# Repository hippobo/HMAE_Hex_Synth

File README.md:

# HMAE_Hex_Synth

Hex Synth project with resistive touch pads based on ekkoflok hex synth project : https://www.ekkoflok.dk/hex.php

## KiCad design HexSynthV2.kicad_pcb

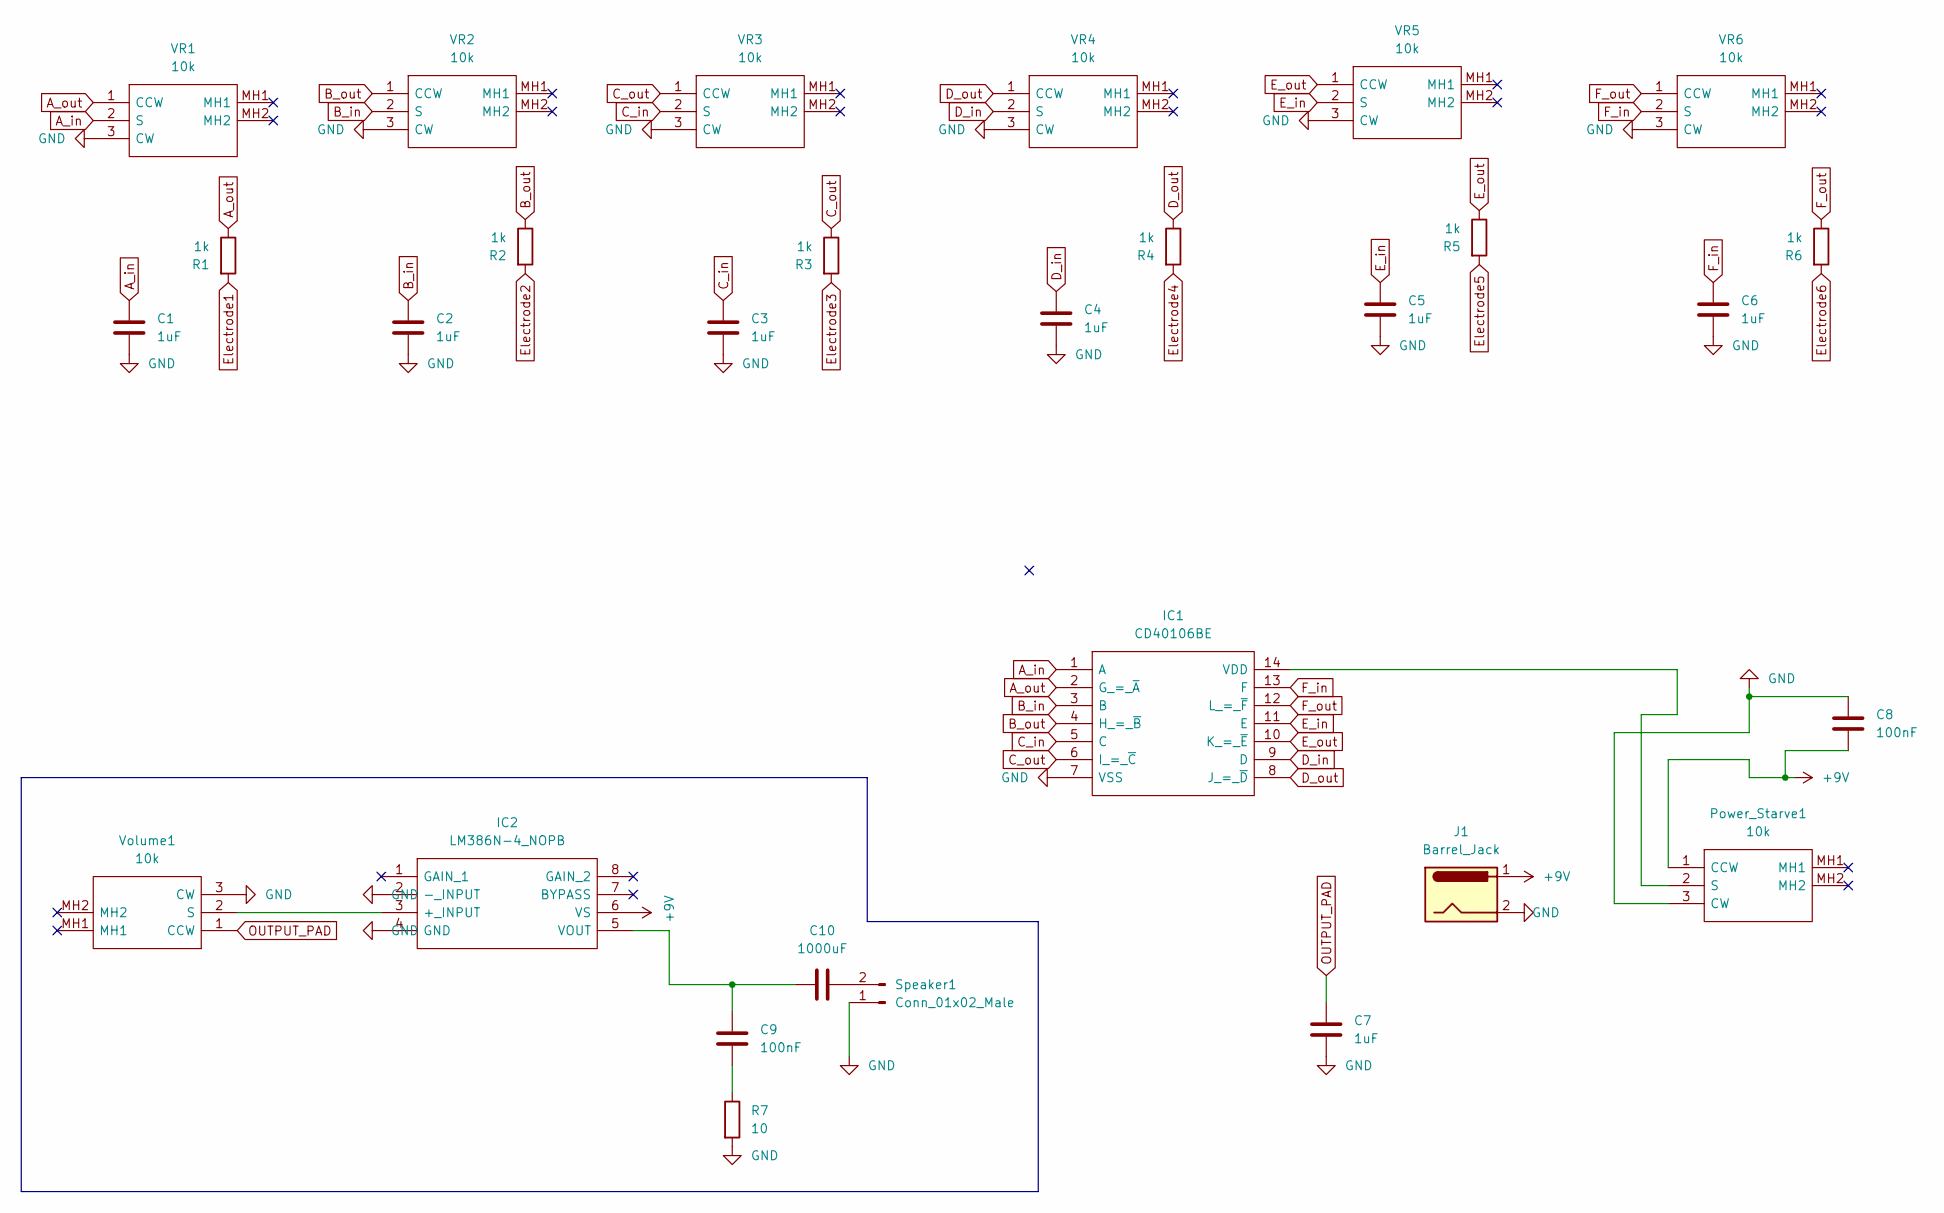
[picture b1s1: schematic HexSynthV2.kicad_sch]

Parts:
C1, C2, C3, C4, C5, C6, C7: 1uF; CP_Radial_D5.0mm_P2.50mm
C8, C9: 100nF; CP_Radial_D5.0mm_P2.50mm
C10: 1000uF; CP_Radial_D8.0mm_P5.00mm
IC1: CD40106BE; DIP794W53P254L1930H508Q14N; Mouser Part Number 595-CD40106BE
IC2: LM386N-4_NOPB; DIP794W53P254L959H508Q8N; Mouser Part Number 926-LM386N-4/NOPB
J1: Barrel_Jack; BarrelJack_Horizontal
Power_Starve1: 10k; P120PKY25BR10K; Mouser Part Number 858-P120PKY25BR10K
R1, R2, R3, R4, R5, R6: 1k; R_Axial_DIN0204_L3.6mm_D1.6mm_P2.54mm_Vertical
R7: 10; R_Axial_DIN0204_L3.6mm_D1.6mm_P2.54mm_Vertical
Speaker1: Conn_01x02_Male; PinHeader_1x02_P2.54mm_Vertical
VR1, VR2, VR3, VR4, VR5, VR6: 10k; P120PKY25BR10K; Mouser Part Number 858-P120PKY25BR10K
Volume1: 10k; P120PKY25BR10K; Mouser Part Number 858-P120PKY25BR10K

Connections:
+9V: C8.1, IC2.6 (VS), J1.1, Power_Starve1.1 (CCW)
A_in: C1.1, IC1.1 (A), VR1.2 (S)
A_out: IC1.2 (G_=_~A), R1.1, VR1.1 (CCW)
B_in: C2.1, IC1.3 (B), VR2.2 (S)
B_out: IC1.4 (H_=_~B), R2.1, VR2.1 (CCW)
C_in: C3.1, IC1.5 (C), VR3.2 (S)
C_out: IC1.6 (I_=_~C), R3.1, VR3.1 (CCW)
D_in: C4.1, IC1.9 (D), VR4.2 (S)
D_out: IC1.8 (J_=_~D), R4.1, VR4.1 (CCW)
E_in: C5.1, IC1.11 (E), VR5.2 (S)
E_out: IC1.10 (K_=_~E), R5.1, VR5.1 (CCW)
Electrode1: R1.2
Electrode2: R2.2
Electrode3: R3.2
Electrode4: R4.2
Electrode5: R5.2
Electrode6: R6.2
F_in: C6.1, IC1.13 (F), VR6.2 (S)
F_out: IC1.12 (L_=_~F), R6.1, VR6.1 (CCW)
GND: C1.2, C2.2, C3.2, C4.2, C5.2, C6.2, C7.2, C8.2, IC1.7 (VSS), IC2.2 (-_INPUT), IC2.4 (GND), J1.2, Power_Starve1.3 (CW), R7.2, Speaker1.1, VR1.3 (CW), VR2.3 (CW), VR3.3 (CW), VR4.3 (CW), VR5.3 (CW), VR6.3 (CW), Volume1.3 (CW)
unnamed: C9.1, R7.1
unnamed: C9.2, C10.1, IC2.5 (VOUT)
unnamed: C10.2, Speaker1.2
unnamed: IC1.14 (VDD), Power_Starve1.2 (S)
unnamed: IC2.3 (+_INPUT), Volume1.2 (S)
OUTPUT_PAD: C7.1, Volume1.1 (CCW)

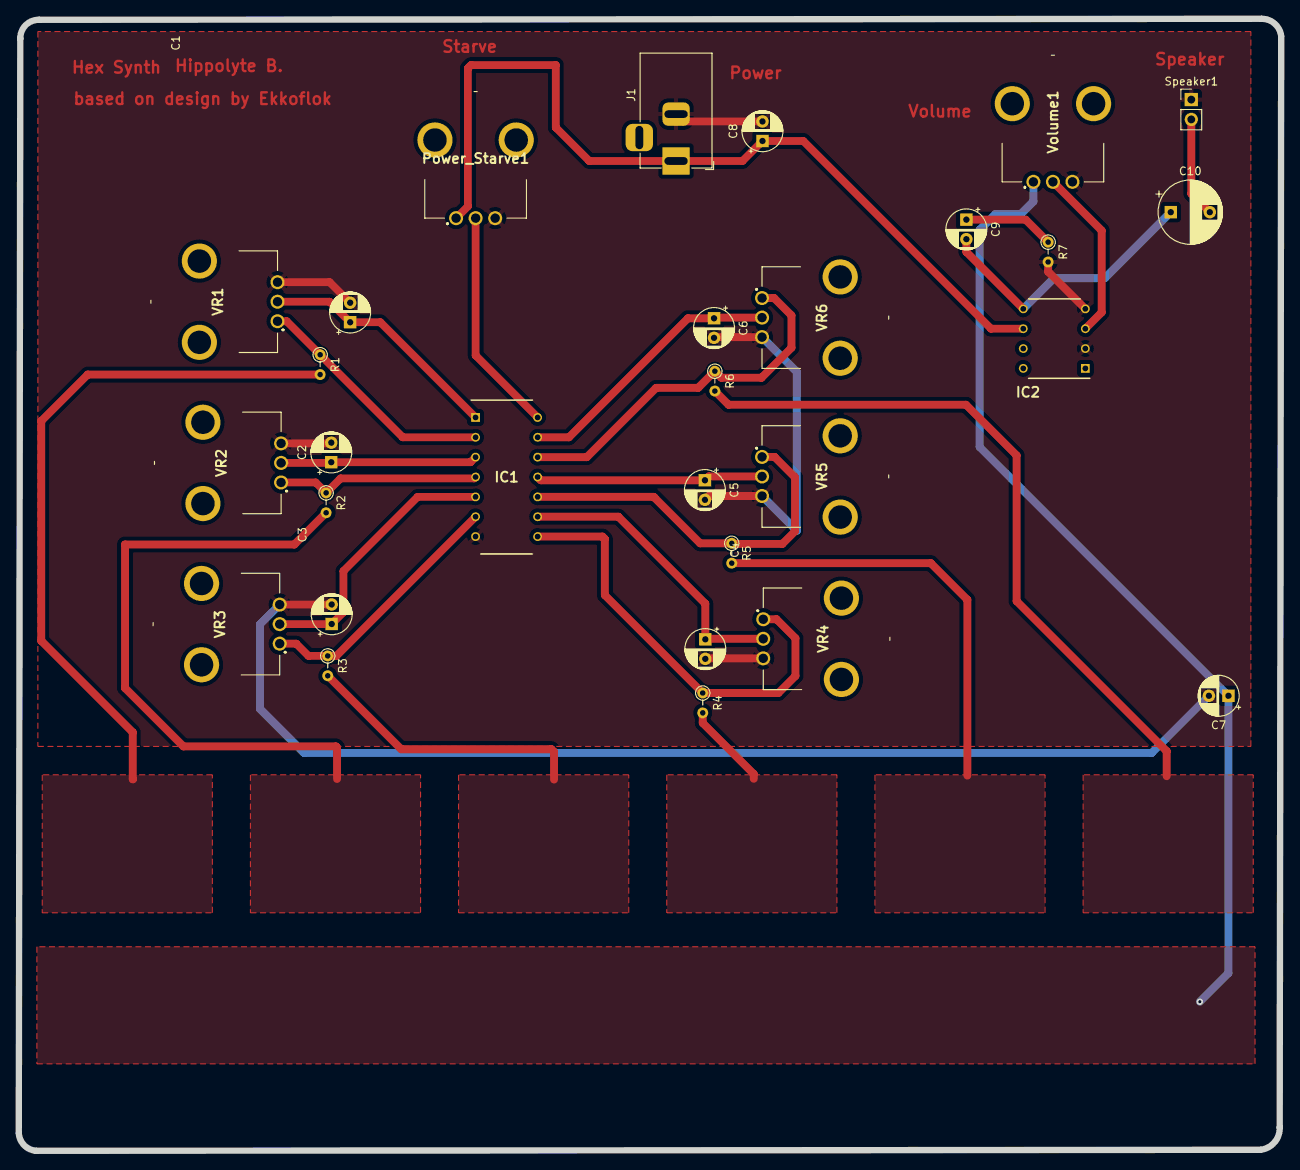
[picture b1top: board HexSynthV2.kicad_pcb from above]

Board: 2 copper layers, 161.5 x 144.8 mm, 29 parts (0 on the bottom side), 20 nets.

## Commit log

2023-03-24 Added Kicad files
